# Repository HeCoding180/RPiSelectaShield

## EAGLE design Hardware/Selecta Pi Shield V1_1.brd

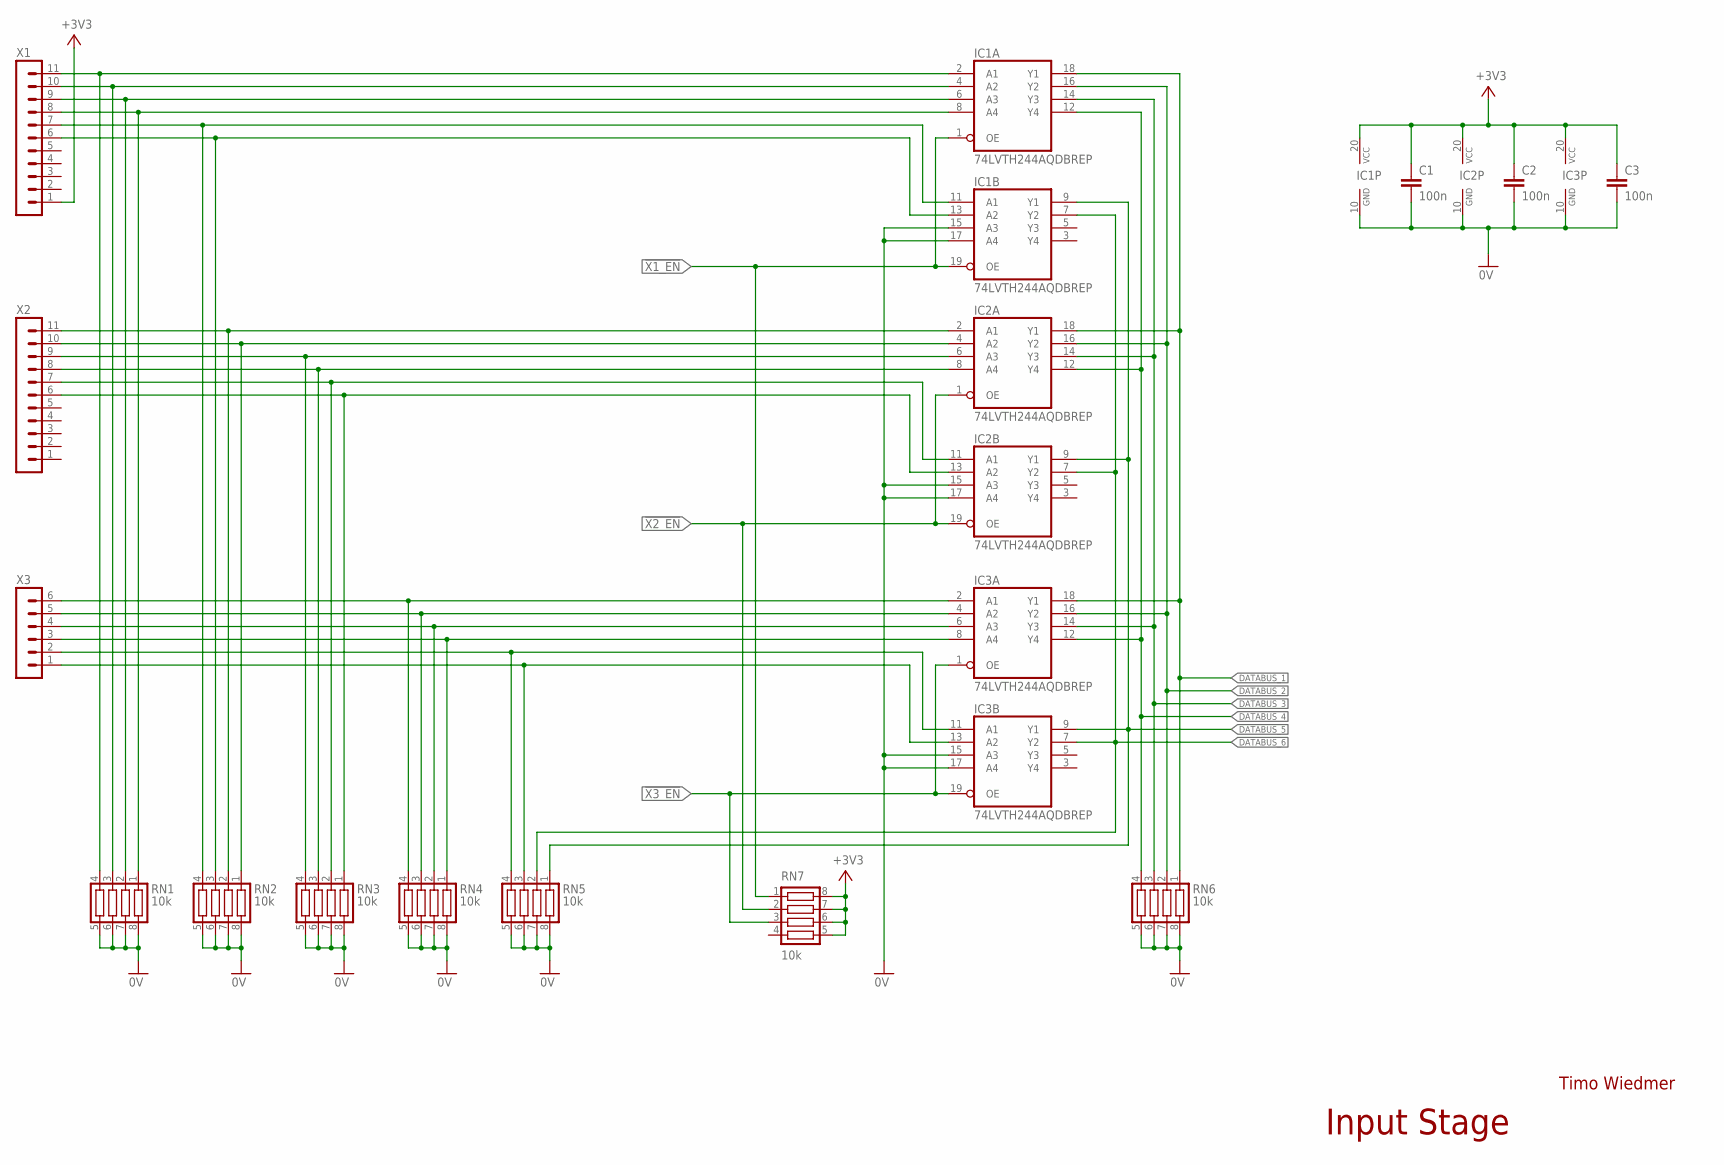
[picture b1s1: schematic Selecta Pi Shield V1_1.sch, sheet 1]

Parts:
C1, C2, C3: 100n; C0603
IC1, IC2, IC3: 74LVTH244AQDBREP; SSOP20
RN1, RN2, RN3, RN4, RN5, RN6, RN7: 10k; CTS742C083
X1, X2: MA11-1
X3: MA06-1

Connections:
0V: C1.2, C2.2, C3.2, IC1.10 (GND), IC1.15 (A3), IC1.17 (A4), IC2.10 (GND), IC2.15 (A3), IC2.17 (A4), IC3.10 (GND), IC3.15 (A3), IC3.17 (A4), RN1.5, RN1.6, RN1.7, RN1.8, RN2.5, RN2.6, RN2.7, RN2.8, RN3.5, RN3.6, RN3.7, RN3.8, RN4.5, RN4.6, RN4.7, RN4.8, RN5.5, RN5.6, RN5.7, RN5.8, RN6.5, RN6.6, RN6.7, RN6.8; also elsewhere on the board
!X1_EN: IC1.1 (OE), IC1.19 (OE), RN7.1; also elsewhere on the board
!X2_EN: IC2.1 (OE), IC2.19 (OE), RN7.2; also elsewhere on the board
!X3_EN: IC3.1 (OE), IC3.19 (OE), RN7.3; also elsewhere on the board
+3V3: C1.1, C2.1, C3.1, IC1.20 (VCC), IC2.20 (VCC), IC3.20 (VCC), RN7.5, RN7.6, RN7.7, RN7.8, X1.1; also elsewhere on the board
B_SELECT1: IC3.2 (A1), RN4.4, X3.6
B_SELECT2: IC3.4 (A2), RN4.3, X3.5
B_SELECT3: IC3.6 (A3), RN4.2, X3.4
B_SELECT4: IC3.8 (A4), RN4.1, X3.3
B_SELECT5: IC3.11 (A1), RN5.4, X3.2
B_SELECT6: IC3.13 (A2), RN5.3, X3.1
DATABUS_1: IC1.18 (Y1), IC2.18 (Y1), IC3.18 (Y1), RN6.1; also elsewhere on the board
DATABUS_2: IC1.16 (Y2), IC2.16 (Y2), IC3.16 (Y2), RN6.2; also elsewhere on the board
DATABUS_3: IC1.14 (Y3), IC2.14 (Y3), IC3.14 (Y3), RN6.3; also elsewhere on the board
DATABUS_4: IC1.12 (Y4), IC2.12 (Y4), IC3.12 (Y4), RN6.4; also elsewhere on the board
DATABUS_5: IC1.9 (Y1), IC2.9 (Y1), IC3.9 (Y1), RN5.1; also elsewhere on the board
DATABUS_6: IC1.7 (Y2), IC2.7 (Y2), IC3.7 (Y2), RN5.2; also elsewhere on the board
unnamed: IC1.2 (A1), RN1.4, X1.11
unnamed: IC1.4 (A2), RN1.3, X1.10
unnamed: IC1.6 (A3), RN1.2, X1.9
unnamed: IC1.8 (A4), RN1.1, X1.8
unnamed: IC2.2 (A1), RN2.2, X2.11
unnamed: IC2.4 (A2), RN2.1, X2.10
unnamed: IC2.6 (A3), RN3.4, X2.9
unnamed: IC2.8 (A4), RN3.3, X2.8
unnamed: IC1.11 (A1), RN2.4, X1.7
unnamed: IC1.13 (A2), RN2.3, X1.6
unnamed: IC2.11 (A1), RN3.2, X2.7
unnamed: IC2.13 (A2), RN3.1, X2.6

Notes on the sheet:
Timo Wiedmer
Input Stage

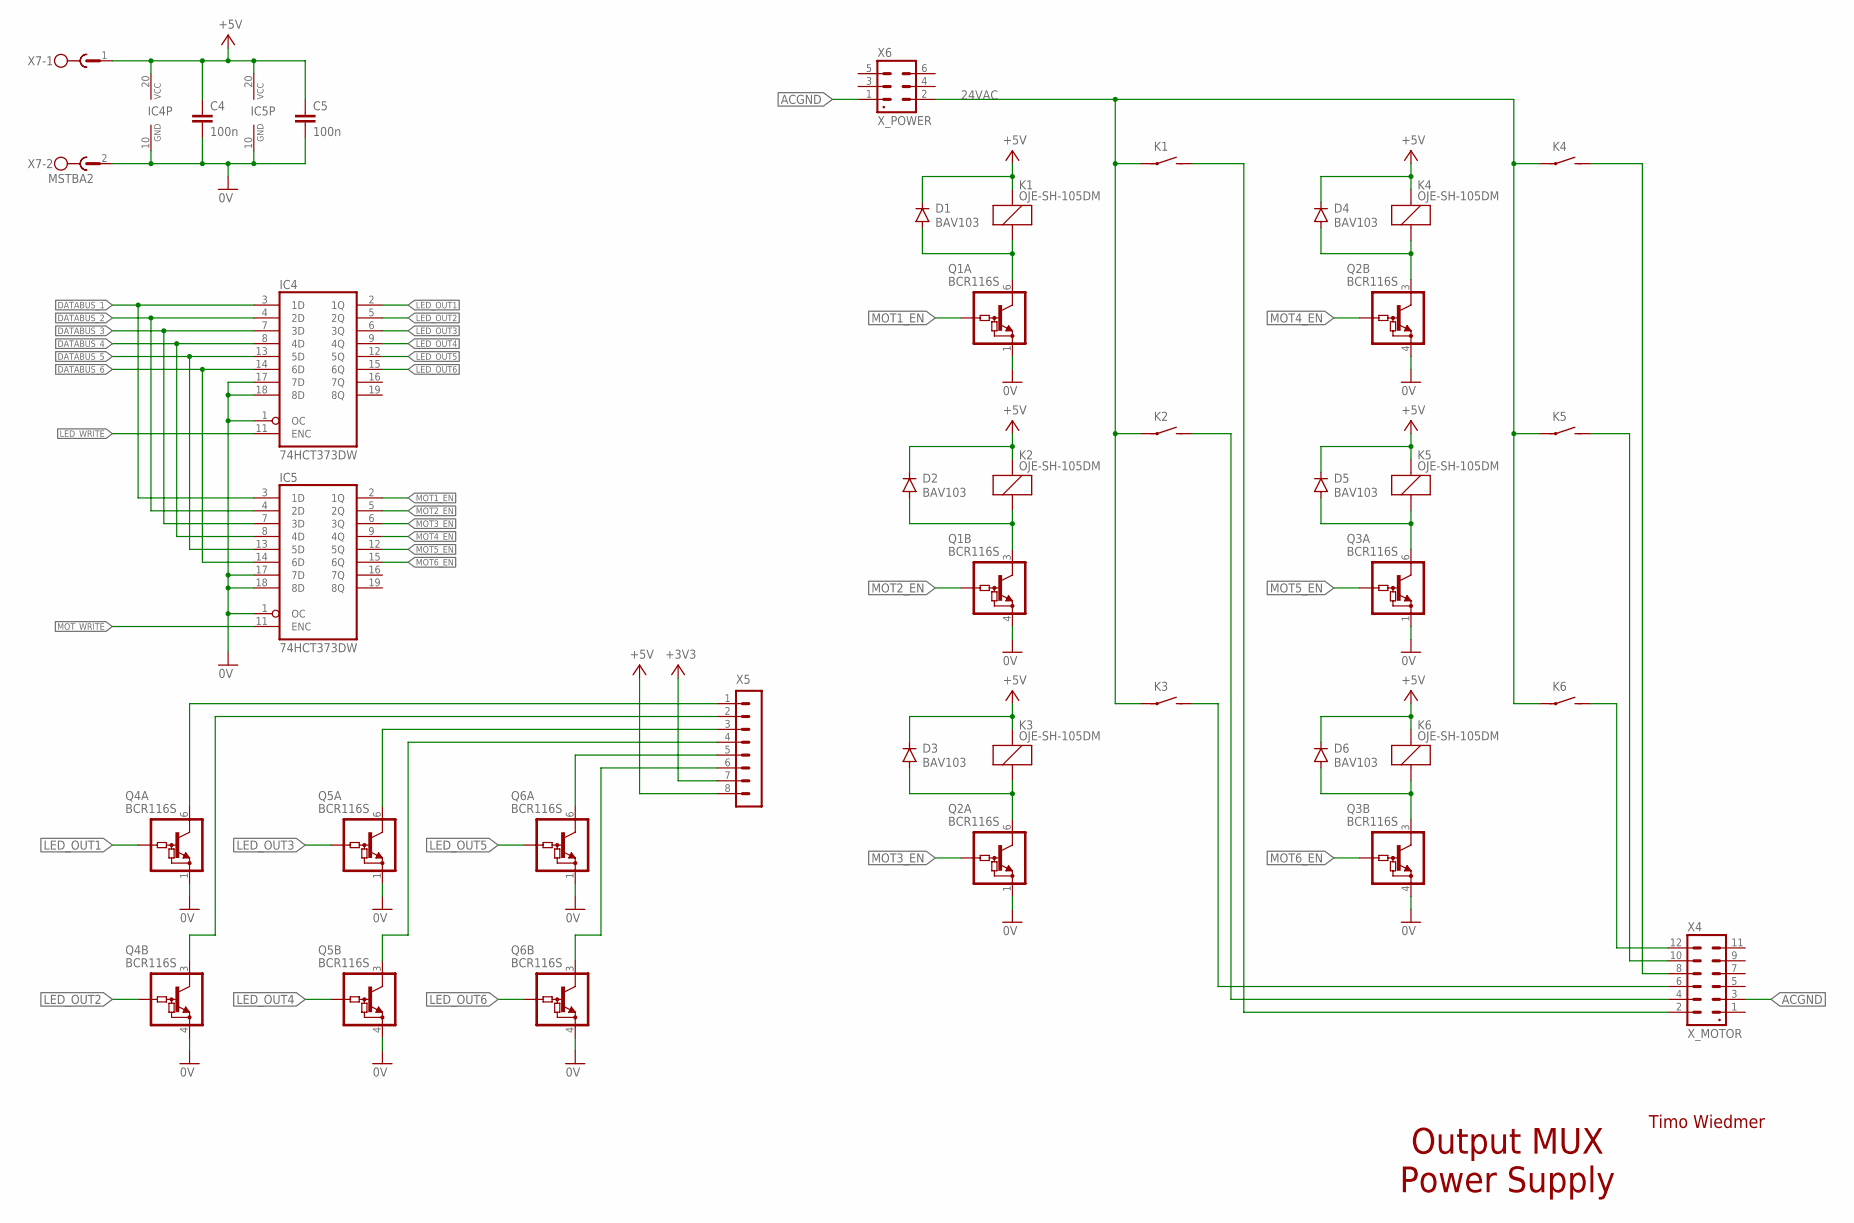
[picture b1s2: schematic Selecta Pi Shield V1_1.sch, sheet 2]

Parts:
C4, C5: 100n; C0603
D1, D2, D3, D4, D5, D6: BAV103; SOD-123_MINI-SMA
IC4, IC5: 74HCT373DW; SO20W
K1, K2, K3, K4, K5, K6: OJE-SH-105DM
Q1, Q2, Q3, Q4, Q5, Q6: BCR116S; SOT363
X4: X_MOTOR; 12P_MINI_FIT
X5: MA08-1
X6: X_POWER; 6P_MINI_FIT
X7: MSTBA2

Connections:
0V: C4.2, C5.2, IC4.1 (OC), IC4.10 (GND), IC4.17 (7D), IC4.18 (8D), IC5.1 (OC), IC5.10 (GND), IC5.17 (7D), IC5.18 (8D), Q1.1 (E), Q1.4 (E), Q2.1 (E), Q2.4 (E), Q3.1 (E), Q3.4 (E), Q4.1 (E), Q4.4 (E), Q5.1 (E), Q5.4 (E), Q6.1 (E), Q6.4 (E), X7.2; also elsewhere on the board
24VAC: K1.COM, K2.COM, K3.COM, K4.COM, K5.COM, K6.COM, X6.2
24VAC_MOT1: K1.NO, X4.2
24VAC_MOT2: K2.NO, X4.4
24VAC_MOT3: K3.NO, X4.6
24VAC_MOT4: K4.NO, X4.8
24VAC_MOT5: K5.NO, X4.10
24VAC_MOT6: K6.NO, X4.12
+3V3: X5.7; also elsewhere on the board
+5V: C4.1, C5.1, D1.C, D2.C, D3.C, D4.C, D5.C, D6.C, IC4.20 (VCC), IC5.20 (VCC), K1.COILA (1), K2.COILA (1), K3.COILA (1), K4.COILA (1), K5.COILA (1), K6.COILA (1), X5.8, X7.1; also elsewhere on the board
ACGND: X4.3, X6.1
DATABUS_1: IC4.3 (1D), IC5.3 (1D); also elsewhere on the board
DATABUS_2: IC4.4 (2D), IC5.4 (2D); also elsewhere on the board
DATABUS_3: IC4.7 (3D), IC5.7 (3D); also elsewhere on the board
DATABUS_4: IC4.8 (4D), IC5.8 (4D); also elsewhere on the board
DATABUS_5: IC4.13 (5D), IC5.13 (5D); also elsewhere on the board
DATABUS_6: IC4.14 (6D), IC5.14 (6D); also elsewhere on the board
LED1: Q4.6 (C), X5.1
LED2: Q4.3 (C), X5.2
LED3: Q5.6 (C), X5.3
LED4: Q5.3 (C), X5.4
LED5: Q6.6 (C), X5.5
LED6: Q6.3 (C), X5.6
LED_OUT1: IC4.2 (1Q), Q4.2 (B)
LED_OUT2: IC4.5 (2Q), Q4.5 (B)
LED_OUT3: IC4.6 (3Q), Q5.2 (B)
LED_OUT4: IC4.9 (4Q), Q5.5 (B)
LED_OUT5: IC4.12 (5Q), Q6.2 (B)
LED_OUT6: IC4.15 (6Q), Q6.5 (B)
LED_WRITE: IC4.11 (ENC); also elsewhere on the board
MOT1_EN: IC5.2 (1Q), Q1.2 (B)
MOT2_EN: IC5.5 (2Q), Q1.5 (B)
MOT3_EN: IC5.6 (3Q), Q2.2 (B)
MOT4_EN: IC5.9 (4Q), Q2.5 (B)
MOT5_EN: IC5.12 (5Q), Q3.2 (B)
MOT6_EN: IC5.15 (6Q), Q3.5 (B)
MOT_WRITE: IC5.11 (ENC); also elsewhere on the board
unnamed: D3.A, K3.COILB (2), Q2.6 (C)
unnamed: D6.A, K6.COILB (2), Q3.3 (C)
unnamed: D5.A, K5.COILB (2), Q3.6 (C)
unnamed: D2.A, K2.COILB (2), Q1.3 (C)
unnamed: D1.A, K1.COILB (2), Q1.6 (C)
unnamed: D4.A, K4.COILB (2), Q2.3 (C)

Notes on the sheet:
Timo Wiedmer
Output MUX Power Supply

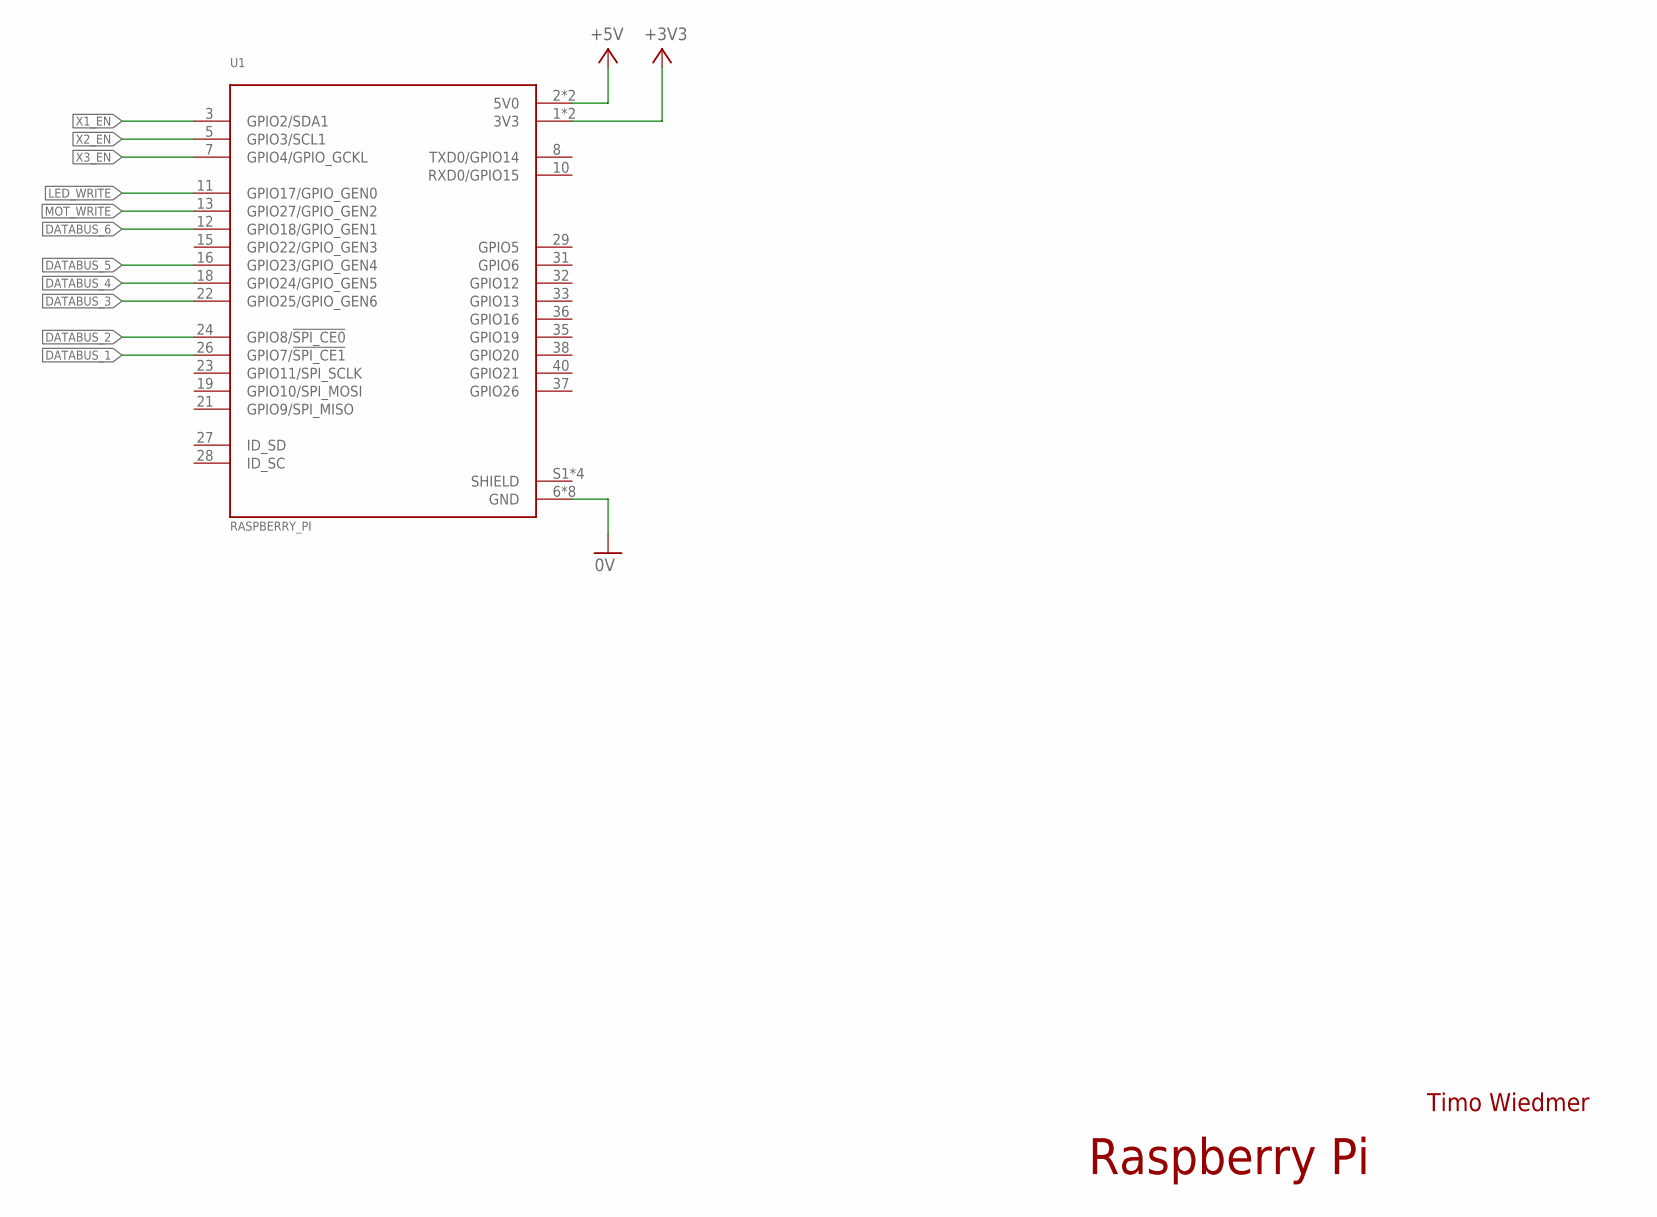
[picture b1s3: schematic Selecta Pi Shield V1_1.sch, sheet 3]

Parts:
U1: RASPBERRY_PI

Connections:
0V: U1.6 (GND), U1.9 (GND), U1.14 (GND), U1.20 (GND), U1.25 (GND), U1.30 (GND), U1.34 (GND), U1.39 (GND); also elsewhere on the board
!X1_EN: U1.3 (GPIO2/SDA1); also elsewhere on the board
!X2_EN: U1.5 (GPIO3/SCL1); also elsewhere on the board
!X3_EN: U1.7 (GPIO4/GPIO_GCKL); also elsewhere on the board
+3V3: U1.1 (3V3), U1.17 (3V3); also elsewhere on the board
+5V: U1.2 (5V0), U1.4 (5V0); also elsewhere on the board
DATABUS_1: U1.26 (GPIO7/!SPI_CE1!); also elsewhere on the board
DATABUS_2: U1.24 (GPIO8/!SPI_CE0!); also elsewhere on the board
DATABUS_3: U1.22 (GPIO25/GPIO_GEN6); also elsewhere on the board
DATABUS_4: U1.18 (GPIO24/GPIO_GEN5); also elsewhere on the board
DATABUS_5: U1.16 (GPIO23/GPIO_GEN4); also elsewhere on the board
DATABUS_6: U1.12 (GPIO18/GPIO_GEN1); also elsewhere on the board
LED_WRITE: U1.11 (GPIO17/GPIO_GEN0); also elsewhere on the board
MOT_WRITE: U1.13 (GPIO27/GPIO_GEN2); also elsewhere on the board
SHIELD: U1.S1 (SHIELD), U1.S2 (SHIELD), U1.S3 (SHIELD), U1.S4 (SHIELD)

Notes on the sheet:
Timo Wiedmer
Raspberry Pi

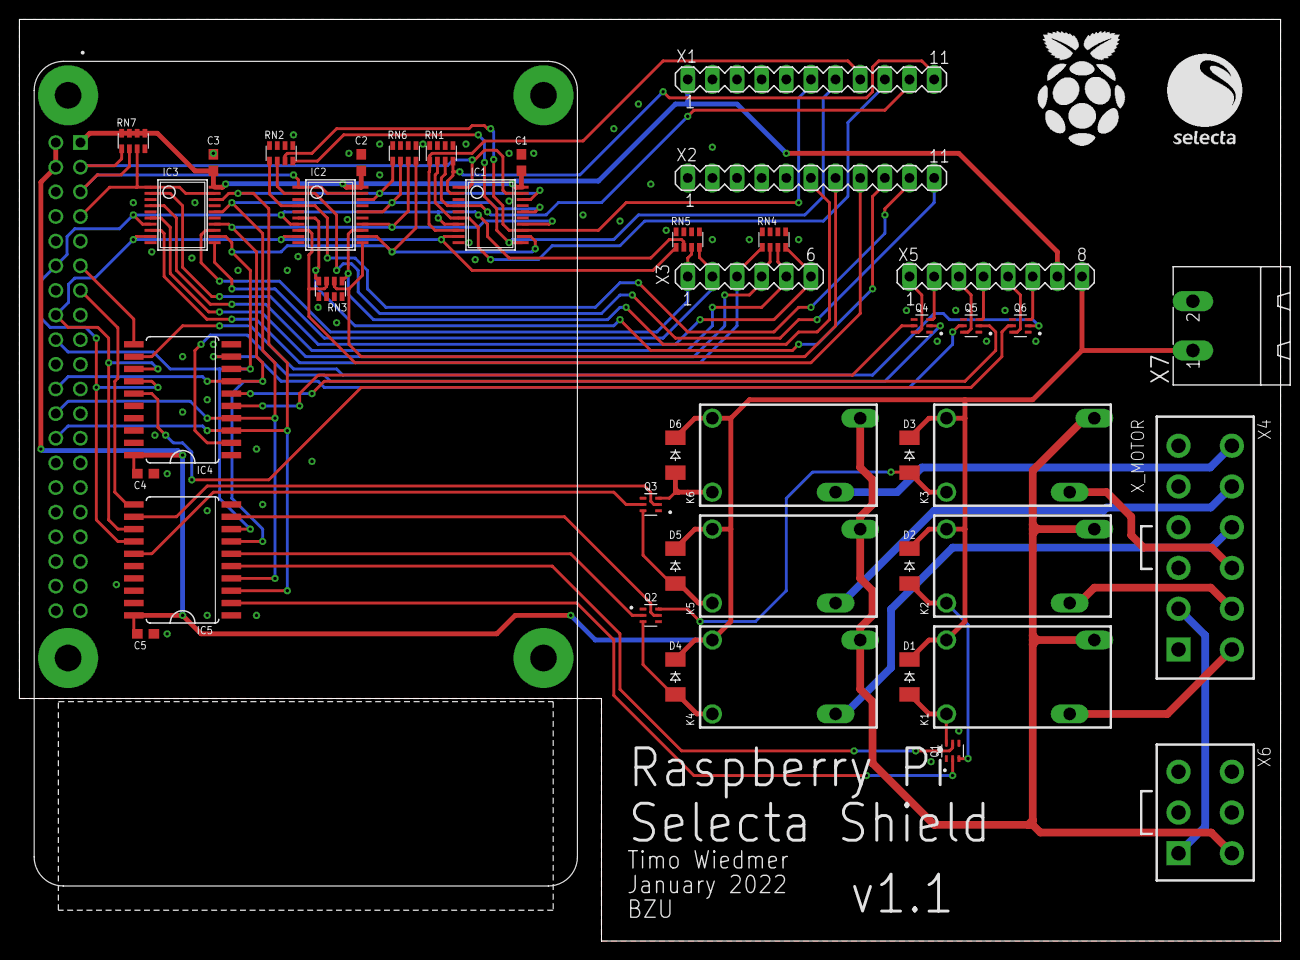
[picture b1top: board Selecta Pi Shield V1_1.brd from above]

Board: 2 copper layers, 130.0 x 95.0 mm, 45 parts (0 on the bottom side), 65 nets.

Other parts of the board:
U$1: RASPBERRY_LOGO
U$2: SELECTA_LOGO

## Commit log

2022-01-24 small issues fixed, simplifications added
    readData() and some other small issues fixed.
    replaced all self.ON with GPIO.HIGH, replaced all self.OFF with GPIO.LOW
2022-01-24 Moved static functions into class
2022-01-24 Made critical variables private
2022-01-24 Library Cleanup
2022-01-24 PCB Design Files V1.0 were added
2022-01-24 Selecta Shield Example Code Added
2022-03-21 Current Limitation Added
    Current limitation added by limiting the amount of motors used at once to 1 motor.
2022-03-21 motor limit console notification added
2022-07-05 Version: v1.1 Push
2025-07-06 Create LICENSE
